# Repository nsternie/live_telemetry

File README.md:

# live_telmetry
Home for all data related to the live telemetry project. Firmware, Gui, and board designs,

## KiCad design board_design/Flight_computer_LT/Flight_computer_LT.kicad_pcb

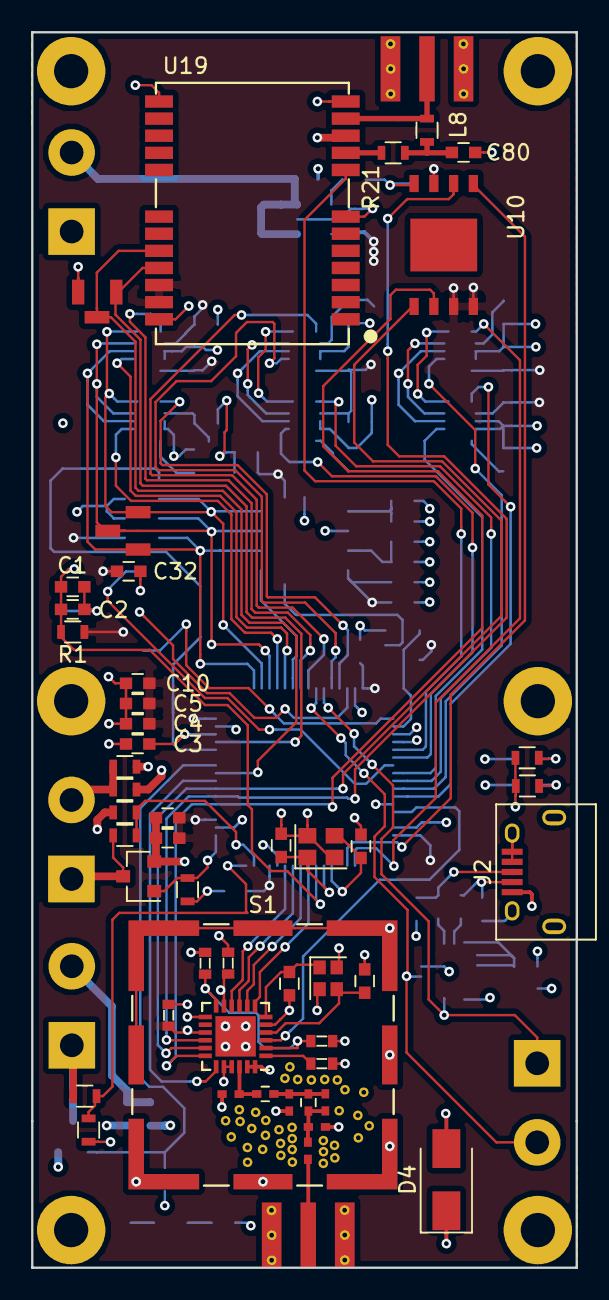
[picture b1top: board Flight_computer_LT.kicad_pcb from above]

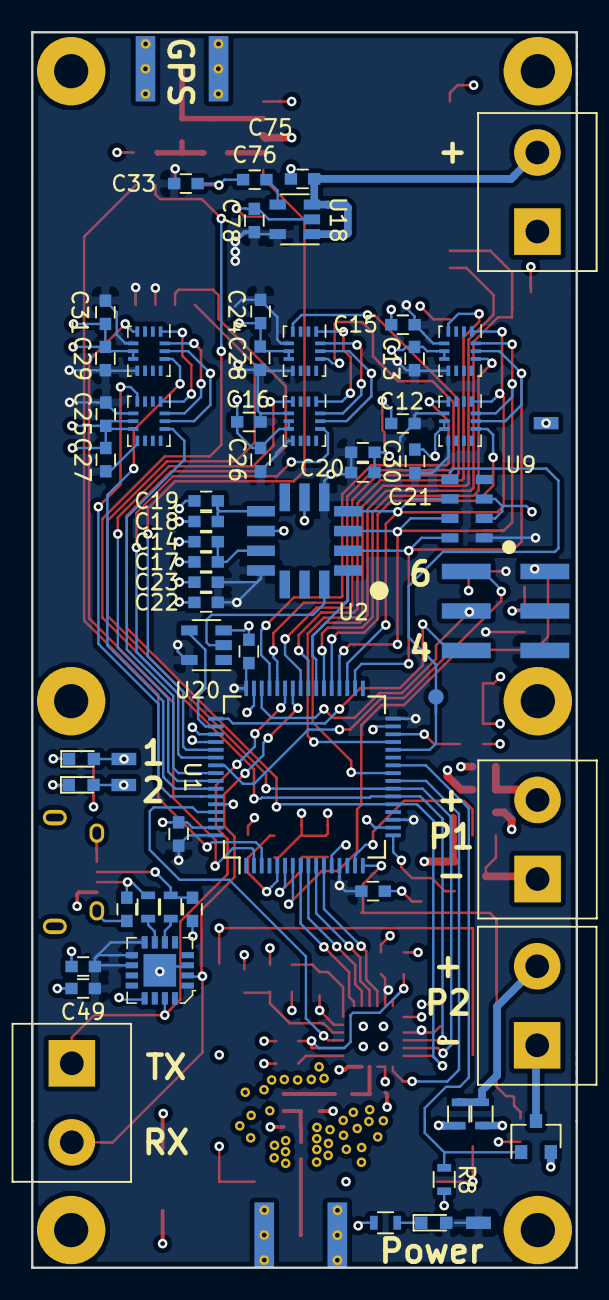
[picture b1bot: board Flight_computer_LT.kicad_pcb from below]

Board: 4 copper layers, 35.0 x 79.4 mm, 124 parts (63 on the bottom side), 76 nets.

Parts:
C1, C5, C6, C7, C8, C9, C12, C13, C14, C15, C16, C18, C20, C22, C24, C25, C26, C27, C28, C29, C30, C31, C32, C33, C36: 100nF; C_0603
C2, C10, C11: 2.2nF; C_0603
C3, C78: 2.2uF; C_0603
C4: 10uF; C_0603
C17, C19, C21, C23, C75: 1uF; C_0603
C34, C35: 47pF; C_0603
C37, C39: 10nF; 0603
C38, C41: 100nF; 0603
C40: 470nF; 0603
C42: 0.8pF; C_0402_NoSilk
C43, C45: 1.2pF; C_0402_NoSilk
C44: 0.5pF; C_0402_NoSilk
C46: 100pF; C_0402_NoSilk
C47, C48: DNP; C_0603
C49: 4.7uF; C_0603
C76: 470pF; C_0603
C77, C82: 15pF; C_0603
C80: 10nF; C_0603
D1, D2, D3: LED; LED_0603
D4: B130-13-F; D_SMA
J1, J4, J7, J8: Screw Term; TerminalBlock_bornier-2_P5.08mm
J2: USB_OTG; USB_Micro-B
J3: Conn_Coaxial; EBAY_SMA
J5: Conn_02x03_Top_Bottom; 2X6_SMA_HEADER_2.54mm
J14: SMA_EDGE; EBAY_SMA
L1: 3nH; C_0402
L2: 2.5nH; C_0402
L8: 27nH; L_0603
M1, M2, M3, M4, M5, M6: M2.5; MountingHole_2.2mm_M2_Pad
Q3, Q4: DMN3023L-7; SOT-23
R1: 3.3K; R_0603
R2, R3: 27; R_0603
R4, R5, R8, R9, R23: 1K; R_0603
R10, R11, R13, R14: 0; R_0603
R12, R15: 20K; R_0603
R16, R17: 10K; R_0603
R21: 10; R_0603
S1: Shield - BMI-S-102; Laird_Technologies_BMI-S-102_16.50x16.50mm
T1, T2, T3, T4, T5, T8, T9, T10, T11, T12: TP; 0603_TP
T28: TEST_1P; PAD_TP_1mm
U1: STM32F446RET6; LQFP-64_10x10mm_Pitch0.5mm
U2: ADXL357
U3, U4, U5, U6, U7, U8: BMG250; Bosch_LGA-14_3x2.5mm_Pitch0.5mm
U9: MS5607
U10: W25N01GVZEIG; 8-WSON_8x6
U11: SX1280; QFN-24-1EP_4x4mm_Pitch0.5mm
U12: FT230XQ-R; WQFN-16-1EP_4x4mm
U18: MIC5219-3.3; SOT-23-5
U19: UBLOX-M8N
U20: SN74LV1T34; SOT-23-5
Y1: 52MHz FW520WFMT1CT-ND; Crystal_SMD_2016-4pin_2.0x1.6mm
Y2: 24MHz 402F2401XIAR; Crystal_SMD_2520-4pin_2.5x2.0mm

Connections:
3V3: C4.1, C5.1, C6.1, C7.1, C8.1, C9.1, C10.1, C11.1, C12.1, C13.1, C15.1, C16.1, C20.1, C21.1, C22.1, C23.1, C24.1, C25.1, C26.1, C27.1, C28.1, C29.1, C30.1, C31.1, C32.1, C33.1, C36.1, C38.1, C41.1, C49.1, C78.1, D2.2, J5.1, R1.1, T8.1, U1.13, U1.19, U1.32, U1.48, U1.64, U2.5, U2.11, U3.5, U3.8, U4.5, U4.8, U5.5, U5.8, U6.5, U6.8, U7.5, U7.8, U8.5, U8.8, U9.1, U10.3, U10.7, U10.8, U11.11, U11.15, U12.1, U12.8, U12.9, U12.10, U18.5, U19.22, U19.23, U20.5
/Connectors/USB_N: R3.1, U12.7
/Connectors/USB_P: R2.1, U12.6
/Radio/LDO_OUT: C37.1, C40.1, U11.2, U11.12
/Radio/XTA: C48.1, U11.4, Y1.3
/Radio/XTB: C47.1, U11.6, Y1.1
BUSY_Radio: U1.8, U11.7
CS_ADXL: U1.39, U2.1
CS_GYRO1: U1.44, U3.12
CS_GYRO2: U1.58, U5.12
CS_GYRO3: U1.56, U7.12
CS_GYRO4: U1.38, U4.12
CS_GYRO5: U1.37, U6.12
CS_GYRO6: U1.54, U8.12
CS_MEM: U1.3, U10.1
CS_MS5607: T28.1, U1.28, U9.5
CS_Radio: U1.24, U11.19
DIO1_Radio: U1.9, U11.8
DIO2_Radio: U1.10, U11.9
DIO3_Radio: U1.11, U11.10
DRDY_ADXL: U1.50, U20.4
GND: C1.2, C2.2, C3.2, C4.2, C5.2, C6.2, C7.2, C8.2, C9.2, C10.2, C11.2, C12.2, C13.2, C14.2, C15.2, C16.2, C17.2, C18.2, C19.2, C20.2, C21.2, C22.2, C23.2, C24.2, C25.2, C26.2, C27.2, C28.2, C29.2, C30.2, C31.2, C32.2, C33.2, C34.2, C35.2, C36.2, C37.2, C38.2, C39.2, C40.2, C41.2, C42.2, C43.2, C45.2, C47.2, C48.2, C49.2, C75.2, C76.2, C77.2, C78.2, C80.2, C82.2, J1.1, J2.4, J2.5, J2.6, J3.2, J5.2, J14.2, M1.1, M2.1, M3.1, M4.1, M5.1, M6.1, Q3.2, Q4.2, R4.2, R5.2, R8.2, R9.2, R11.1, R14.1, R16.1, R17.1, R23.2, S1.1, T11.1, T12.1, U1.12, U1.18, U1.31, U1.47, U1.60, U1.63, U2.6, U2.9, U3.6, U3.7, U4.6, U4.7, U5.6, U5.7, U6.6, U6.7, U7.6, U7.7, U8.6, U8.7, U9.2, U9.3, U10.4, U11.5, U11.13, U11.20, U11.21, U11.23, U11.24, U11.25, U12.3, U12.13, U12.17, U18.2, U19.7, U19.10, U19.12, U19.13, U19.24, U20.3, Y1.2, Y1.4, Y2.2, Y2.4
GPS_nRST: U1.53, U19.8
GYRO1_INT: U1.41, U3.4
GYRO2_INT: U1.2, U5.4
GYRO3_INT: U1.59, U7.4
GYRO4_INT: U1.40, U4.4
GYRO5_INT: U1.45, U6.4
GYRO6_INT: U1.57, U8.4
LED1: D3.2, T5.1, U1.51
LED2: D1.2, T4.1, U1.52
MISO1: U1.22, U10.2, U11.16
MISO2: T3.1, U1.35, U2.4, U3.1, U4.1, U5.1, U6.1, U7.1, U8.1, U9.6
MOSI1: U1.23, U10.5, U11.17
MOSI2: T2.1, U1.36, U2.3, U3.14, U4.14, U5.14, U6.14, U7.14, U8.14, U9.7
unnamed: C3.1, U1.30
unnamed: C14.1, C17.1, U2.10
unnamed: C18.1, C19.1, U2.8
unnamed: C34.1, J2.3, R2.2
unnamed: C35.1, J2.2, R3.2
unnamed: C39.1, U11.1
unnamed: C42.1, L1.2, U11.22
unnamed: C43.1, C44.1, L1.1, L2.2
unnamed: C44.2, C45.1, C46.1, L2.1
unnamed: C46.2, J3.1
unnamed: C76.1, U18.4
unnamed: C77.1, U1.6, Y2.1
unnamed: C80.1, L8.1, R21.2
unnamed: C82.1, U1.5, Y2.3
unnamed: D1.1, R4.1
unnamed: D2.1, R23.1
unnamed: D3.1, R5.1
unnamed: D4.2, J2.1
unnamed: J7.1, Q3.3, R12.2
unnamed: J7.2, R10.2, R11.2
unnamed: J8.1, Q4.3, R15.2
unnamed: J8.2, R13.2, R14.2
unnamed: J14.1, L8.2, U19.11
unnamed: R21.1, U19.9
unnamed: U2.14, U20.2
PYRO_1_FIRE: Q3.1, R8.1, U1.26
PYRO_1_SENSE: R12.1, R16.2, U1.16
PYRO_2_FIRE: Q4.1, R9.1, U1.17
PYRO_2_SENSE: R15.1, R17.2, U1.15
SCLK1: U1.21, U10.6, U11.18
SCLK2: T1.1, U1.34, U2.2, U3.13, U4.13, U5.13, U6.13, U7.13, U8.13, U9.8
SWO: J5.6, U1.55
TCK: J5.4, U1.49
TMS: J5.5, U1.46
USART_RX1: T9.1, U1.25, U19.20
USART_RX3: J4.1, U1.43, U12.15
USART_TX1: T10.1, U1.29, U19.21
USART_TX3: J4.2, U1.42, U12.2
VIN: C75.1, D4.1, J1.2, R10.1, R13.1, U18.1, U18.3
nRST: C1.1, C2.1, J5.3, R1.2, U1.7
nRST_RADIO: U1.61, U11.3

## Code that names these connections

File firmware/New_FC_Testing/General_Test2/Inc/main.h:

/**
  ******************************************************************************
  * File Name          : main.hpp
  * Description        : This file contains the common defines of the application
  ******************************************************************************
  ** This notice applies to any and all portions of this file
  * that are not between comment pairs USER CODE BEGIN and
  * USER CODE END. Other portions of this file, whether 
  * inserted by the user or by software development tools
  * are owned by their respective copyright owners.
  *
  * COPYRIGHT(c) 2017 STMicroelectronics
  *
  * Redistribution and use in source and binary forms, with or without modification,
  * are permitted provided that the following conditions are met:
  *   1. Redistributions of source code must retain the above copyright notice,
  *      this list of conditions and the following disclaimer.
  *   2. Redistributions in binary form must reproduce the above copyright notice,
  *      this list of conditions and the following disclaimer in the documentation
  *      and/or other materials provided with the distribution.
  *   3. Neither the name of STMicroelectronics nor the names of its contributors
  *      may be used to endorse or promote products derived from this software
  *      without specific prior written permission.
  *
  * THIS SOFTWARE IS PROVIDED BY THE COPYRIGHT HOLDERS AND CONTRIBUTORS "AS IS"
  * AND ANY EXPRESS OR IMPLIED WARRANTIES, INCLUDING, BUT NOT LIMITED TO, THE
  * IMPLIED WARRANTIES OF MERCHANTABILITY AND FITNESS FOR A PARTICULAR PURPOSE ARE
  * DISCLAIMED. IN NO EVENT SHALL THE COPYRIGHT HOLDER OR CONTRIBUTORS BE LIABLE
  * FOR ANY DIRECT, INDIRECT, INCIDENTAL, SPECIAL, EXEMPLARY, OR CONSEQUENTIAL
  * DAMAGES (INCLUDING, BUT NOT LIMITED TO, PROCUREMENT OF SUBSTITUTE GOODS OR
  * SERVICES; LOSS OF USE, DATA, OR PROFITS; OR BUSINESS INTERRUPTION) HOWEVER
  * CAUSED AND ON ANY THEORY OF LIABILITY, WHETHER IN CONTRACT, STRICT LIABILITY,
  * OR TORT (INCLUDING NEGLIGENCE OR OTHERWISE) ARISING IN ANY WAY OUT OF THE USE
  * OF THIS SOFTWARE, EVEN IF ADVISED OF THE POSSIBILITY OF SUCH DAMAGE.
  *
  ******************************************************************************
  */
/* Define to prevent recursive inclusion -------------------------------------*/
#ifndef __MAIN_H
#define __MAIN_H
  /* Includes ------------------------------------------------------------------*/

/* Includes ------------------------------------------------------------------*/
/* USER CODE BEGIN Includes */

/* USER CODE END Includes */

/* Private define ------------------------------------------------------------*/

#define PYRO_2_FIRE_Pin GPIO_PIN_13
#define PYRO_2_FIRE_GPIO_Port GPIOC
#define PYRO_2_SENSE_Pin GPIO_PIN_0
#define PYRO_2_SENSE_GPIO_Port GPIOC
#define PYRO_4_SENSE_Pin GPIO_PIN_1
#define PYRO_4_SENSE_GPIO_Port GPIOC
#define PYRO_4_FIRE_Pin GPIO_PIN_2
#define PYRO_4_FIRE_GPIO_Port GPIOC
#define PA_EN_Pin GPIO_PIN_3
#define PA_EN_GPIO_Port GPIOC
#define LNA_EN_Pin GPIO_PIN_0
#define LNA_EN_GPIO_Port GPIOA
#define PYRO_1_SENSE_Pin GPIO_PIN_1
#define PYRO_1_SENSE_GPIO_Port GPIOA
#define PYRO_3_FIRE_Pin GPIO_PIN_2
#define PYRO_3_FIRE_GPIO_Port GPIOA
#define PYRO_3_SENSE_Pin GPIO_PIN_3
#define PYRO_3_SENSE_GPIO_Port GPIOA
#define PYRO_1_FIRE_Pin GPIO_PIN_4
#define PYRO_1_FIRE_GPIO_Port GPIOA
#define CS_MEM_Pin GPIO_PIN_4
#define CS_MEM_GPIO_Port GPIOC
#define INT1_ADXL_Pin GPIO_PIN_0
#define INT1_ADXL_GPIO_Port GPIOB
#define DRDY_ADXL_Pin GPIO_PIN_1
#define DRDY_ADXL_GPIO_Port GPIOB
#define CS_ADXL_Pin GPIO_PIN_2
#define CS_ADXL_GPIO_Port GPIOB
#define GPS_nRST_Pin GPIO_PIN_12
#define GPS_nRST_GPIO_Port GPIOB
#define CS_MS5607_Pin GPIO_PIN_8
#define CS_MS5607_GPIO_Port GPIOC
#define GYRO5_INT_Pin GPIO_PIN_9
#define GYRO5_INT_GPIO_Port GPIOC
#define GYRO3_INT_Pin GPIO_PIN_8
#define GYRO3_INT_GPIO_Port GPIOA
#define CS_GYRO2_Pin GPIO_PIN_11
#define CS_GYRO2_GPIO_Port GPIOA
#define GYRO2_INT_Pin GPIO_PIN_12
#define GYRO2_INT_GPIO_Port GPIOA
#define TMS_Pin GPIO_PIN_13
#define TMS_GPIO_Port GPIOA
#define TCK_Pin GPIO_PIN_14
#define TCK_GPIO_Port GPIOA
#define CS_GYRO4_Pin GPIO_PIN_15
#define CS_GYRO4_GPIO_Port GPIOA
#define GYRO4_INT_Pin GPIO_PIN_10
#define GYRO4_INT_GPIO_Port GPIOC
#define CS_GYRO1_Pin GPIO_PIN_11
#define CS_GYRO1_GPIO_Port GPIOC
#define GYRO6_INT_Pin GPIO_PIN_2
#define GYRO6_INT_GPIO_Port GPIOD
#define SWO_Pin GPIO_PIN_3
#define SWO_GPIO_Port GPIOB
#define GYRO1_INT_Pin GPIO_PIN_4
#define GYRO1_INT_GPIO_Port GPIOB
#define CS_GYRO6_Pin GPIO_PIN_5
#define CS_GYRO6_GPIO_Port GPIOB
#define CS_GYRO3_Pin GPIO_PIN_6
#define CS_GYRO3_GPIO_Port GPIOB
#define CS_GYRO5_Pin GPIO_PIN_7
#define CS_GYRO5_GPIO_Port GPIOB
#define CS_CC1125_Pin GPIO_PIN_8
#define CS_CC1125_GPIO_Port GPIOB
#define GPIO0_Pin GPIO_PIN_9
#define GPIO0_GPIO_Port GPIOB

/* ########################## Assert Selection ############################## */
/**
  * @brief Uncomment the line below to expanse the "assert_param" macro in the 
  *        HAL drivers code
  */
/* #define USE_FULL_ASSERT    1U */

/* USER CODE BEGIN Private defines */

/* USER CODE END Private defines */

#ifdef __cplusplus
 extern "C" {
#endif
void _Error_Handler(char *, int);

#define Error_Handler() _Error_Handler(__FILE__, __LINE__)
#ifdef __cplusplus
}
#endif

/**
  * @}
  */ 

/**
  * @}
*/ 

#endif /* __MAIN_H */
/************************ (C) COPYRIGHT STMicroelectronics *****END OF FILE****/

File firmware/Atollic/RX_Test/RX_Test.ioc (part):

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Mcu.Name=STM32F446R(C-E)Tx
Mcu.Package=LQFP64
Mcu.UserName=STM32F446RETx
PA1.GPIOParameters=GPIO_Label
PA1.GPIO_Label=PYRO_2_SENSE
PA1.Signal=ADCx_IN1
PA10.Mode=Asynchronous
PA10.Signal=USART1_RX
PA11.GPIOParameters=GPIO_Speed,GPIO_Label
PA11.GPIO_Label=GYRO1_CS
PA11.GPIO_Speed=GPIO_SPEED_FREQ_HIGH
PA11.Signal=GPIO_Output
PA12.GPIOParameters=GPIO_Label
PA12.GPIO_Label=GYRO5_INT
PA12.Signal=GPXTI12
PA13.Mode=Trace_Asynchronous_SW
PA13.Signal=SYS_JTMS-SWDIO
PA14.Mode=Trace_Asynchronous_SW
PA14.Signal=SYS_JTCK-SWCLK
PA15.GPIOParameters=GPIO_Label
PA15.GPIO_Label=ADXL_DRDY
PA15.Signal=GPXTI15
PA2.GPIOParameters=GPIO_Label
PA2.GPIO_Label=PYRO_1_SENSE
PA2.Signal=ADCx_IN2
PA3.GPIOParameters=GPIO_Label
PA3.GPIO_Label=PYRO_2_FIRE
PA3.Signal=GPIO_Output
PA5.Mode=Full_Duplex_Master
PA5.Signal=SPI1_SCK
PA6.Mode=Full_Duplex_Master
PA6.Signal=SPI1_MISO
PA7.Mode=Full_Duplex_Master
PA7.Signal=SPI1_MOSI
PA8.GPIOParameters=GPIO_Label
PA8.GPIO_Label=GYRO1_INT
PA8.Signal=GPXTI8
PA9.Mode=Asynchronous
PA9.Signal=USART1_TX
PB0.GPIOParameters=GPIO_Label
PB0.GPIO_Label=PYRO_1_FIRE
PB0.Signal=GPIO_Output
PB10.Mode=Asynchronous
PB10.Signal=USART3_TX
PB13.Mode=Full_Duplex_Master
PB13.Signal=SPI2_SCK
PB14.Mode=Full_Duplex_Master
PB14.Signal=SPI2_MISO
PB15.Mode=Full_Duplex_Master
PB15.Signal=SPI2_MOSI
PB2.GPIOParameters=GPIO_Speed,GPIO_Label
PB2.GPIO_Label=MS5607_CS
PB2.GPIO_Speed=GPIO_SPEED_FREQ_HIGH
PB2.Signal=GPIO_Output
PB3.Mode=Trace_Asynchronous_SW
PB3.Signal=SYS_JTDO-SWO
PB4.GPIOParameters=GPIO_Speed,GPIO_Label
PB4.GPIO_Label=GYRO3_CS
PB4.GPIO_Speed=GPIO_SPEED_FREQ_HIGH
PB4.Signal=GPIO_Output
PB5.GPIOParameters=GPIO_Label
PB5.GPIO_Label=GYRO6_INT
PB5.Signal=GPXTI5
PB6.GPIOParameters=GPIO_Speed,GPIO_Label
PB6.GPIO_Label=GYRO2_CS
PB6.GPIO_Speed=GPIO_SPEED_FREQ_HIGH
PB6.Signal=GPIO_Output
PB7.GPIOParameters=GPIO_Label
PB7.GPIO_Label=GYRO3_INT
PB7.Signal=GPXTI7
PB8.GPIOParameters=GPIO_Label
PB8.GPIO_Label=nRST_RADIO
PB8.Signal=GPIO_Output
PC0.GPIOParameters=GPIO_Label
PC0.GPIO_Label=BUSY_Radio
PC0.Signal=GPIO_Input
PC1.GPIOParameters=GPIO_Label
PC1.GPIO_Label=DIO1_Radio
PC1.Signal=GPXTI1
PC10.GPIOParameters=GPIO_Label
PC10.GPIO_Label=LED1
PC10.Signal=GPIO_Output
PC11.GPIOParameters=GPIO_Label
PC11.GPIO_Label=LED2
PC11.Signal=GPIO_Output
PC12.GPIOParameters=GPIO_Label
PC12.GPIO_Label=GPS_nRST
PC12.Signal=GPIO_Output
PC13.GPIOParameters=GPIO_Label
PC13.GPIO_Label=GYRO2_INT
PC13.Signal=GPXTI13
PC14-OSC32_IN.GPIOParameters=GPIO_Speed,GPIO_Label
PC14-OSC32_IN.GPIO_Label=MEM_CS
PC14-OSC32_IN.GPIO_Speed=GPIO_SPEED_FREQ_LOW
PC14-OSC32_IN.Signal=GPIO_Output
PC2.GPIOParameters=GPIO_Label
PC2.GPIO_Label=DIO2_Radio
PC2.Signal=GPXTI2
PC3.GPIOParameters=GPIO_Label
PC3.GPIO_Label=DIO3_Radio
PC3.Signal=GPXTI3
PC4.GPIOParameters=GPIO_Label
PC4.GPIO_Label=CS_Radio
PC4.Signal=GPIO_Output
PC5.Mode=Asynchronous
PC5.Signal=USART3_RX
PC6.GPIOParameters=GPIO_Speed,GPIO_Label
PC6.GPIO_Label=GYRO5_CS
PC6.GPIO_Speed=GPIO_SPEED_FREQ_HIGH
PC6.Signal=GPIO_Output
PC7.GPIOParameters=GPIO_Speed,GPIO_Label
PC7.GPIO_Label=GYRO4_CS
PC7.GPIO_Speed=GPIO_SPEED_FREQ_HIGH
PC7.Signal=GPIO_Output
PC8.GPIOParameters=GPIO_Speed,GPIO_Label
PC8.GPIO_Label=ADXL_CS
PC8.GPIO_Speed=GPIO_SPEED_FREQ_HIGH
PC8.Signal=GPIO_Output
PC9.GPIOParameters=GPIO_Label
PC9.GPIO_Label=GYRO4_INT
PC9.Signal=GPXTI9
PD2.GPIOParameters=GPIO_Speed,GPIO_Label
PD2.GPIO_Label=GYRO6_CS
PD2.GPIO_Speed=GPIO_SPEED_FREQ_HIGH
PD2.Signal=GPIO_Output
RCC.SYSCLKFreq_VALUE=180000000
RCC.SYSCLKSource=RCC_SYSCLKSOURCE_PLLCLK
board=RX_Test

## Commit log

2017-10-23 Adds gitignore
2017-10-23 Adding basic foolder stucture
2017-10-23 Adds kicad project skeleton
2017-10-23 Adds kicad library for project
2017-10-23 Adds STM32F446RET6 to lib
2017-10-29 Permissions Test
    Test of permissions
2017-10-29 Added existing source
    Added existing source code I had already been working on.
2017-10-29 Added W25N01GV
    Added 1 Gbit SPI flash chip (W25N01GV)
2017-10-29 Started schematic and added symbols
    Added STM32F446RE to schematic and added supporting passives. Added
    symbol for MS5607 barometer.
2017-10-30 Split sch into pages
    Split schematic into pages. Also added BMG250 gyro symbol to lib.
2017-10-30 Added hiarchal sheets for various sensors
2017-10-30 Deleted bad spelling
2017-10-31 Added Radio Schematic
    Copied radio schematic from circuit maker. Cleaned up sch a bit by
    changing part symbols. Needs to be verified.
2017-11-01 Added gyro array
    Added 6 BMG250s. Also deleted connector previously used for radio, which
    is now onboard.
2017-11-05 Added 2W PA and power stuff
    Added 2W PA and ldos to generate 5 and 3.3V power.
2017-11-07 Added GPS
    Added ublox gps schematic.
2017-11-09 Updated connector page
2017-11-10 Added uC connections
    Connected a bunch of stuff to uC. Pin list is on drive. Still WIP.
    Finished most footprints except accel, which Devin is working on.
2017-11-11 Added Kicad footprints library
2017-11-11 Footprint Associations
2017-11-12 Mid layout
    mid layout checkpoint. Still placing components. No wiring done.
2017-11-12 Component placement in progress
2017-11-13 Has IMU code and other interface stuff
2017-11-13 jk this is
2017-11-14 Continuing layout
    Moved gyros and accel into actual positions.
2017-11-15 Mid route
    Routing gyro area. Currently dumpster fire. From chaos comes order.
2017-11-16 Routing
    Routing still in progress. Startting to look a little bit better.
2017-11-19 General Routing Done
    Routing done. Need to clean up everything and add testpoints.
2017-11-19 Tieing up loose ends
    Cleaning up board/sch and working on checklist.
2017-11-19 Adding Test Points
2017-11-21 Cleaning
    Cleaning up sch and pcb.
2017-12-07 added Enceladus project
2017-12-29 Board changes
2018-01-10 Adding core project folder
2018-01-10 Created project
2018-01-11 Programs
2018-01-11 Flash files
2018-01-11 Flash things
2018-01-11 Added flash reset
2018-01-11 Basic flash functionality working
2018-01-12 Added data struct file
2018-01-12 Added commandline files
2018-01-13 Whatever I worked on last night :)
2018-01-13 Changes write_buffer to random program data in order to not overwrite settings
2018-01-17 Flash stuff :)
2018-01-18 Added command stuff from the engine controller code base
2018-01-20 Sensor Changes
    Added code for accel and baro.
2018-01-20 New branch
2018-01-20 initial commit of ground station gui
2018-01-20 Added microsecond timer
2018-01-26 Things from last week
2018-01-27 Add ignore .log files
2018-01-27 Eclsipse things
2018-01-27 Commandline works
2018-01-27 I think I got the ghosts out of the flash.... Hopefully. ~~Tom Marvalo Riddle~~
2018-01-27 minumum viable product
2018-01-27 GPS initial commit
2018-01-27 Added usart 3 IRQ handler and receive buffer
2018-01-27 Silly clock thing again
2018-01-28 Im like Luigi, getting rod of those poltergiests
2018-01-28 numerical fields implemented
2018-01-28 command line input
2018-01-28 serial logging
2018-01-28 unnecessary print
2018-01-28 command logging
2018-01-28 data logging
2018-01-28 Erase block debug
2018-01-28 mach number
2018-01-28 GPS funcionality finished
2018-01-28 1, 2, 3, 4, 5. 1, 2, 3, 4, 5, 6, 7. This is a bad haiku.
2018-01-28 Style
2018-01-28 com port selection
2018-01-29 implemented status bar
2018-01-29 icon
2018-01-29 improved zero alt and status bar
2018-01-29 Added log functions for some sensors
2018-01-29 Adds readfile funtions
2018-01-29 String format change
2018-01-29 Adds scripts folder
2018-01-29 Dont want to commit all data
2018-01-30 Many csvs now
2018-01-30 Also bins
2018-01-30 Many things on the decoding packet side
2018-01-30 Remove log files
2018-01-30 Small post merge changes
2018-01-30 Autoplot things
2018-02-02 Added timers and dready interrupts for gyros and accel.
2018-02-06 Prep for merge
2018-02-06 Adds log_gps function
2018-02-06 Added GPS to decode script
2018-02-09 Cleaned up old project files that were no longer being used to avoid confusion.
2018-02-09 Cleaned up main file.
2018-02-09 Added radio file.
2018-02-10 Added radio stuff. Fixed board_design folder.
2018-02-10 Renames log to log_to_flash to avoid naming conflict
2018-02-10 Added project for ground station.
2018-02-10 Fixing the same problem twice, because... git
2018-02-10 Work on radio stuff.
2018-02-10 Radio testing
2018-02-16 Finished basic transmit radio.
2018-02-17 TX code workign w/ GUI.
2018-02-17 Implemented tabs
    Added tabs to gui in preparation for maps
2018-02-20 multiple new features
    command log tab
    command buttons
    applied new command standards
    time stamp to log box
    commands recieved counter
2018-02-20 updated baudrate and values in dummy
2018-02-20 Revert "updated baudrate and values in dummy"
    This reverts commit f9436dfd34327823331be304b8d484de9baaa7f1.
2018-02-20 Revert "Revert "updated baudrate and values in dummy""
    This reverts commit 75b1cf553f4b4ca82790377cedd4be255a3a348a.
2018-02-20 multiple new features
    - data logging directories
    - command line arguments to initialize run name
    - started on maps
    - command buttons improved
    - commands recieved fully implemented
    - auto scan on start
2018-02-20 added masa logo and reshuffled ui
2018-02-20 exit app properly
2018-02-20 heart beat indcator
2018-03-03 Adding atollic files
2018-03-04 Changing machines
2018-03-04 back
2018-03-04 Adds auto plot to pdf on datadump
2018-03-04 Im a sellout but the accel works now. Whatss 3 bytes anyhow?
2018-03-04 Dont want all those pdfs
2018-03-04 Flash
2018-03-06 Changed gyros to timer based and added delay on init, which seemed to fix init issues.
2018-03-06 Pre merge
2018-03-06 Merging into master
2018-03-06 Ignore data
2018-03-06 Maybe this time, git is killing me
2018-03-06 Lets pick this cherry
2018-03-06 Atollic
2018-03-06 Atollic2
2018-03-06 Meta
2018-03-06 What
2018-03-06 Lets get sloppy
2018-03-06 Only the 4th time I've cloned this repo...
2018-03-06 Metadata sux try 2
2018-03-06 Metadata sux try 3
2018-03-06 kill it (metadata) with fire
2018-03-06 Testing metatdata thing
2018-03-06 Testing metatdata thing 2
2018-03-06 Added commands in main.c in the radio area. Haven't been tested, will test after implementation of commands
2018-03-06 Adds logging calls to readio command handlers
2018-03-07 status byte implemented
2018-03-07 Fixed radio packet len on transmitter
2018-03-07 Increased radio data rate
2018-03-07 Increased radio data rate try 2
2018-03-07 commands
2018-03-07 Put gyro delay back in
2018-03-07 gyro scaling
2018-03-07 accel scaling factor
2018-03-07 hopefully fixed decimal point errors
2018-03-07 minor changes to rounding
2018-03-07 fixed command log
2018-03-07 Changed TX time to 10
2018-03-07 Added some things changed some other things
2018-03-07 Changed GPS logging thing to fixed. Changed uart buad to 921600
2018-03-07 update git ignore
2018-03-08 Added hex generation to ground station. Added RX_PARITY.
2018-03-08 ignore
2018-03-08 Fixed [?] radio issue
2018-03-08 Fixing gitignore
2018-03-08 Revert "Fixing gitignore"
    This reverts commit 1eaba9e6a756ccfc2ad3d51e16f2917715e98921.
2018-03-08 packet loss fix
2018-03-10 New PCB Rev, ready for verification
2018-03-10 Board review notes
2018-03-17 Added projects for TX and RX
2018-03-17 Fixed bugs in RX
2018-03-18 Moved radio files to SX1280.c and .h
2018-03-18 Started changing core to use new radio. Started cleaning up files
2018-03-18 Done w/ first pass of Rocket code
2018-03-18 Working on ground station
2018-03-18 Working on commands
2018-03-18 Working on commands, Rocket side
2018-03-19 Commands and receiver currently working. Moving on to FC TODO list
2018-03-19 Removed old projects
2018-03-19 Changed accel calc to root of sum of squares and added max altitude. Max altitude is incorrect on GUI
2018-03-29 Changed TX power to be safe with 2 amplifiers
2018-03-31 Test
2018-04-01 Pulling changes from old branch
2018-04-06 Added RSSI calculation and changed TX power on rocket side back to 13dbm. Also added a lockout for Baro.
2018-04-06 Added callsign packet every 5 min. Not tested
2018-04-07 Test Flight Version
2018-04-09 added range to target to gui
    use haversine formula to calculate great circle distance to rocket. origin defined by command "setorigin <lat> <long>"
2018-05-31 fix to max accel problem
